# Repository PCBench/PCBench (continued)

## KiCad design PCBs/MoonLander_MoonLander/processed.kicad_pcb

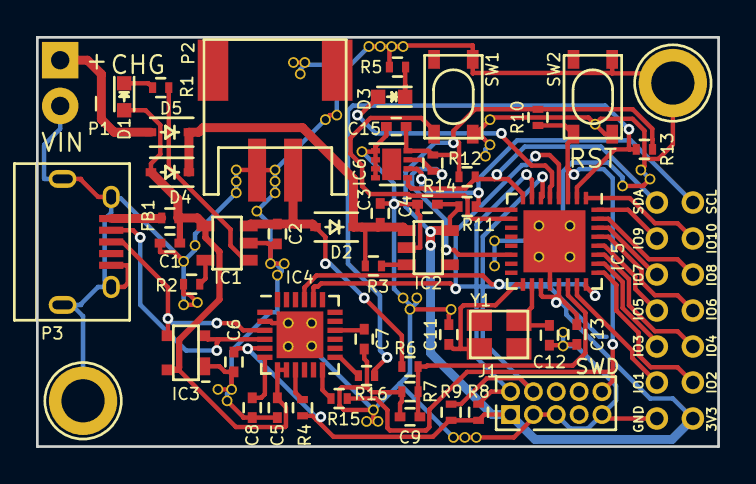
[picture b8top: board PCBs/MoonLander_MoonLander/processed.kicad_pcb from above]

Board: 2 copper layers, 37.8 x 22.7 mm, 51 parts (0 on the bottom side), 43 nets.

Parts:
C1, C2, C3, C4, C5, C8: 1uF; C_0402
C6, C9, C13, C15: 0.1uF; C_0402
C7: 4.7uF; C_0402
C11, C12: 18pF; C_0402
D1, D3: LED; LED-0603
D2, D4, D5: D_Schottky; SOD-323
FB1: FERRITE; R_0402
IC1: MCP73831/2; SSOP5
IC2: BU33SD5; SSOP5
IC3: PRTR5V0U2X; SOT143B
IC4: CP2110-GM; QFN-24-1EP_4x4mm_Pitch0.5mm
IC5: LPC824M201JHI33; QFN-32-1EP_5x5mm_Pitch0.5mm
IC6: 24LCxx; DFN-8-1EP_2x2mm_Pitch0.5mm
J1: Cortex_JTAG/SWD_10; Pin_Header_Straight_2x05_Pitch1.27mm
MH1, MH2: MountingHole; MH-M2
P1: CONN_01X02; Socket_Strip_Straight_1x02
P2: CONN_01X02; JST-LIPO-SMT
P3: USB_OTG; USB_Micro-B
P4: CONN_02X07; Header_2mm_2x7
R1: 1k; R_0402
R2, R4, R8, R9, R10, R11, R12, R14: 10k; R_0402
R3, R6, R7, R13: 100k; R_0402
R5: 470; R_0402
R15, R16: 100; R_0402
SW1, SW2: SW_PUSH; PTS810
Y1: Crystal; crystal_FA238-TSX3225

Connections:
5V_USB: C1.1, C5.1, D1.2, D4.2, FB1.1, IC1.4, IC3.4, IC4.7, IC4.8
/CPU/EEPROM_WP: IC5.14, IC6.7, R14.2
/CPU/I2C0_SCL: IC5.9, IC6.6, P4.13, R11.2
/CPU/I2C0_SDA: IC5.8, IC6.5, P4.14, R12.2
/CPU/ISP_ENTRY: IC4.13, R16.1
/CPU/ISP_RST: IC4.12, R15.2
/CPU/ISP_RXD: IC4.21, IC5.24
/CPU/ISP_TXD: IC4.20, IC5.4
/CPU/LED: D3.2, IC5.5
/CPU/PIO0_6/ADC_1: IC5.23, P4.4
/CPU/PIO0_13/ADC_10: IC5.1, P4.11
/CPU/PIO0_14/ADC_2: IC5.25, P4.3
/CPU/PIO0_17/ADC_9: IC5.32, P4.12
/CPU/PIO0_18/ADC_8: IC5.31, P4.9
/CPU/PIO0_19/ADC_7: IC5.30, P4.10
/CPU/PIO0_20/ADC_6: IC5.29, P4.7
/CPU/PIO0_21/ADC_5: IC5.28, P4.8
/CPU/PIO0_22/ADC_4: IC5.27, P4.5
/CPU/PIO0_23/ADC_3: IC5.26, P4.6
/CPU/RESET: IC5.3, J1.10, R10.2, R15.1, SW2.1
/CPU/SW1: IC5.10, SW1.1
/CPU/SWCLK: IC5.6, J1.4, R9.2
/CPU/SWDIO: IC5.7, J1.2, R8.2
/CPU/V_BAT: C2.1, D2.2, IC1.3, P2.1, R6.1
/PowerSupply/V_EXT: D5.2, P1.1
/USB-Serial/USB_D+: IC3.3, IC4.3, P3.3
/USB-Serial/USB_D-: IC3.2, IC4.4, P3.2
GND: C1.2, C2.2, C3.2, C4.2, C5.2, C6.2, C7.2, C8.1, C9.2, C11.1, C12.1, C13.2, C15.2, IC1.2, IC2.2, IC3.1, IC4.2, IC4.25, IC5.20, IC5.33, IC6.1, IC6.2, IC6.3, IC6.4, J1.3, J1.5, J1.9, MH1.1, MH2.1, P1.2, P2.2, P3.5, P3.6, P4.2, R2.1, R5.2, R7.2, SW1.2, SW2.2
unnamed: C3.1, D2.1, D4.1, D5.1, IC2.1, R3.2
unnamed: C7.1, IC4.16
unnamed: C8.2, IC4.6
unnamed: C9.1, IC5.22, R6.2, R7.1
unnamed: C11.2, IC5.17, Y1.1
unnamed: C12.2, IC5.18, Y1.2
unnamed: D1.1, R1.2
unnamed: D3.1, R5.1
unnamed: FB1.2, P3.1
unnamed: IC1.1, R1.1
unnamed: IC1.5, R2.2
unnamed: IC2.3, R3.1
unnamed: IC4.9, R4.2
unnamed: IC5.2, R13.1, R16.2
VCC: C4.1, C6.1, C13.1, C15.1, IC2.5, IC4.5, IC5.19, IC5.21, IC6.8, J1.1, P4.1, R4.1, R8.1, R9.1, R10.1, R11.1, R12.1, R13.2, R14.1
